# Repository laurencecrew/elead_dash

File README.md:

# elead_dash

Dash module for Honda Lead scooter electric conversion.

Based on STM32Duino for STM32F103C8T6

Design includes:
- Votol EM150SP 'CANbus' controller
- Daly R25A-GI02 BMS CANBus x 2
- SSD1306 OLED 64x48 0.66" SPI x 2
- Original fuel gauge driven by H-bridge / PWM
- See also, elead_lighting for tail light module

See 'Hardware' folder for:
- Bike wiring diagram
- PCB schematics
- Eagle files
- PCB CAM outputs

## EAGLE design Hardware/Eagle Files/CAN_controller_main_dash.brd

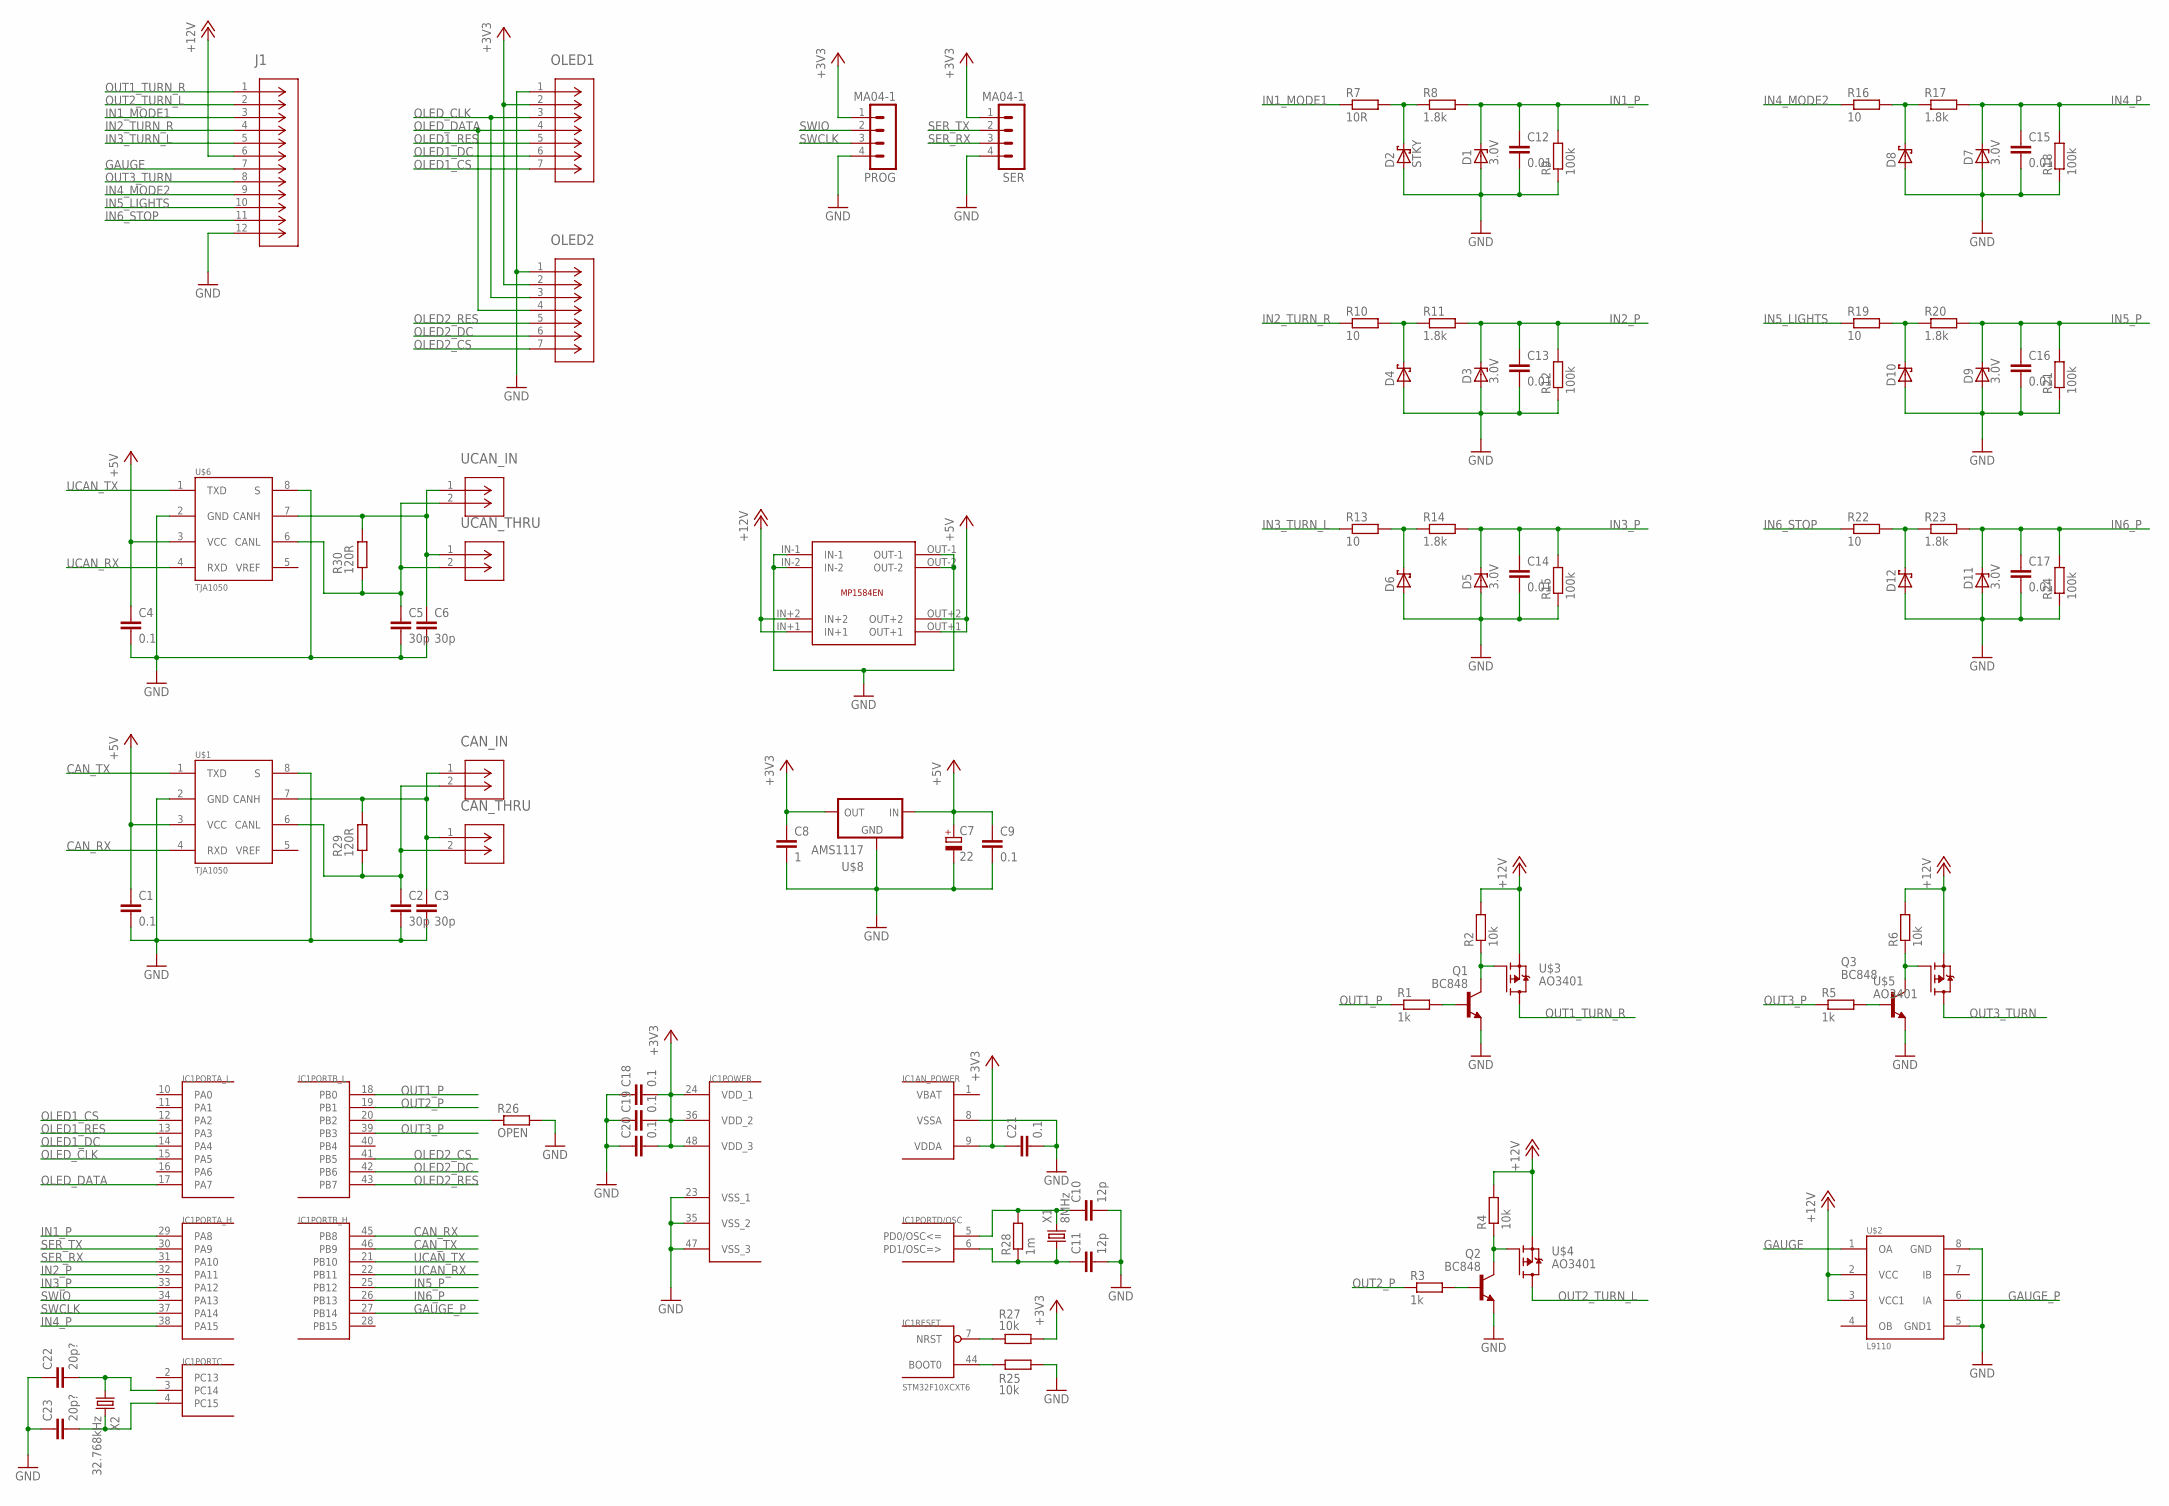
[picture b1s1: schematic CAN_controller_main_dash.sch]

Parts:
C1, C4, C9, C18, C19, C20, C21: 0.1; C0603
C2, C3, C5, C6: 30p; C0603
C7: 22; A/3216-18R
C8: 1; C0805
C10, C11: 12p; C0603
C12, C13, C14, C15, C16, C17: 0.01; C0603
C22, C23: 20p?; C0603
CAN_IN: CAN_IN; CON_2068320202_MOL
CAN_THRU: MOLEX_2068320202; CON_2068320202_MOL
D1, D3, D5, D7, D9, D11: 3.0V; ZD0603
D2: STKY; ZD0603
D4, D6, D8, D10, D12: DIODE_SCHOTTKY; ZD0603
IC1: STM32F10XCXT6; TQFP48
J1: MOLEX_2068321202; CON_2068321202_MOL
OLED1, OLED2: MOLEX_1053091107; CON_1053091107
PROG: MA04-1; 1X04
Q1, Q2, Q3: BC848; SOT23
R1, R3, R5: 1k; R0603
R2, R4, R6, R25, R27: 10k; R0603
R7: 10R; R0603
R8, R11, R14, R17, R20, R23: 1.8k; R0603
R9, R12, R15, R18, R21, R24: 100k; R0603
R10, R13, R16, R19, R22: 10; R0603
R26: OPEN; R0603
R28: 1m; R0603
R29, R30: 120R; R0603
SER: MA04-1; 1X04
U$1, U$6: TJA1050; SO08
U$2: L9110; SO08
U$3, U$4, U$5: AO3401; SOT23
U$7: MP1584_DC-DC_MODULEMINI_22X17; MP1584_DC-DC_MODULE
U$8: AMS1117; SOT223-W
UCAN_IN: MOLEX_2068320202; CON_2068320202_MOL
UCAN_THRU: MOLEX_2068320202; CON_2068320202_MOL
X1: 8MHz; XTAL-ECX-53
X2: 32.768kHz; MM20SS

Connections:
+3V3: C8.1, C18.2, C19.2, C20.2, C21.1, IC1.9 (VDDA), IC1.24 (VDD_1), IC1.36 (VDD_2), IC1.48 (VDD_3), OLED1.2, OLED2.2, PROG.1, R27.2, SER.1, U$8.2 (OUT)
+5V: C1.1, C4.1, C7.+, C9.1, U$1.3 (VCC), U$6.3 (VCC), U$7.OUT+1, U$7.OUT+2, U$8.3 (IN)
+12V: J1.6, R2.2, R4.2, R6.2, U$2.2 (VCC), U$2.3 (VCC1), U$3.2 (S), U$4.2 (S), U$5.2 (S), U$7.IN+1, U$7.IN+2
CANH: C3.1, CAN_IN.1, CAN_THRU.1, R29.2, U$1.7 (CANH)
CANL: C2.1, CAN_IN.2, CAN_THRU.2, R29.1, U$1.6 (CANL)
CAN_RX: IC1.45 (PB8), U$1.4 (RXD)
CAN_TX: IC1.46 (PB9), U$1.1 (TXD)
GAUGE: J1.7, U$2.1 (OA)
GAUGE_P: IC1.27 (PB14), U$2.6 (IA)
GND: C1.2, C2.2, C3.2, C4.2, C5.2, C6.2, C7.-, C8.2, C9.2, C10.2, C11.2, C12.2, C13.2, C14.2, C15.2, C16.2, C17.2, C18.1, C19.1, C20.1, C21.2, C22.1, C23.1, D1.A, D2.A, D3.A, D4.A, D5.A, D6.A, D7.A, D8.A, D9.A, D10.A, D11.A, D12.A, IC1.8 (VSSA), IC1.23 (VSS_1), IC1.35 (VSS_2), IC1.47 (VSS_3), J1.12, OLED1.1, OLED2.1, PROG.4, Q1.2 (E), Q2.2 (E), Q3.2 (E), R9.1, R12.1, R15.1, R18.1, R21.1, R24.1, R25.2, R26.2, SER.4, U$1.2 (GND), U$1.8 (S), U$2.5 (GND1), U$2.8 (GND), U$6.2 (GND), U$6.8 (S), U$7.IN-1, U$7.IN-2, U$7.OUT-1, U$7.OUT-2, U$8.1 (GND)
IN1_MODE1: J1.3, R7.1
IN1_P: C12.1, D1.C, IC1.29 (PA8), R8.2, R9.2
IN2_P: C13.1, D3.C, IC1.32 (PA11), R11.2, R12.2
IN2_TURN_R: J1.4, R10.1
IN3_P: C14.1, D5.C, IC1.33 (PA12), R14.2, R15.2
IN3_TURN_L: J1.5, R13.1
IN4_MODE2: J1.9, R16.1
IN4_P: C15.1, D7.C, IC1.38 (PA15), R17.2, R18.2
IN5_LIGHTS: J1.10, R19.1
IN5_P: C16.1, D9.C, IC1.25 (PB12), R20.2, R21.2
IN6_P: C17.1, D11.C, IC1.26 (PB13), R23.2, R24.2
IN6_STOP: J1.11, R22.1
unnamed: Q2.1 (B), R3.2
unnamed: Q2.3 (C), R4.1, U$4.1 (G)
unnamed: Q3.1 (B), R5.2
unnamed: Q1.1 (B), R1.2
unnamed: Q1.3 (C), R2.1, U$3.1 (G)
unnamed: Q3.3 (C), R6.1, U$5.1 (G)
unnamed: C10.1, IC1.5 (PD0/OSC<=), R28.2, X1.2
unnamed: C11.1, IC1.6 (PD1/OSC=>), R28.1, X1.1
unnamed: D2.C, R7.2, R8.1
unnamed: IC1.44 (BOOT0), R25.1
unnamed: D4.C, R10.2, R11.1
unnamed: IC1.20 (PB2), R26.1
unnamed: IC1.7 (NRST), R27.1
unnamed: D6.C, R13.2, R14.1
unnamed: C22.2, IC1.3 (PC14), X2.1
unnamed: C23.2, IC1.4 (PC15), X2.4 (2)
unnamed: D8.C, R16.2, R17.1
unnamed: D10.C, R19.2, R20.1
unnamed: D12.C, R22.2, R23.1
OLED1_CS: IC1.12 (PA2), OLED1.7
OLED1_DC: IC1.14 (PA4), OLED1.6
OLED1_RES: IC1.13 (PA3), OLED1.5
OLED2_CS: IC1.41 (PB5), OLED2.7
OLED2_DC: IC1.42 (PB6), OLED2.6
OLED2_RES: IC1.43 (PB7), OLED2.5
OLED_CLK: IC1.15 (PA5), OLED1.3, OLED2.3
OLED_DATA: IC1.17 (PA7), OLED1.4, OLED2.4
OUT1_P: IC1.18 (PB0), R1.1
OUT1_TURN_R: J1.1, U$3.3 (D)
OUT2_P: IC1.19 (PB1), R3.1
OUT2_TURN_L: J1.2, U$4.3 (D)
OUT3_P: IC1.39 (PB3), R5.1
OUT3_TURN: J1.8, U$5.3 (D)
SER_RX: IC1.31 (PA10), SER.3
SER_TX: IC1.30 (PA9), SER.2
SWCLK: IC1.37 (PA14), PROG.3
SWIO: IC1.34 (PA13), PROG.2
UCANH: C6.1, R30.2, U$6.7 (CANH), UCAN_IN.1, UCAN_THRU.1
UCANL: C5.1, R30.1, U$6.6 (CANL), UCAN_IN.2, UCAN_THRU.2
UCAN_RX: IC1.22 (PB11), U$6.4 (RXD)
UCAN_TX: IC1.21 (PB10), U$6.1 (TXD)
VBAT: IC1.1 (VBAT)

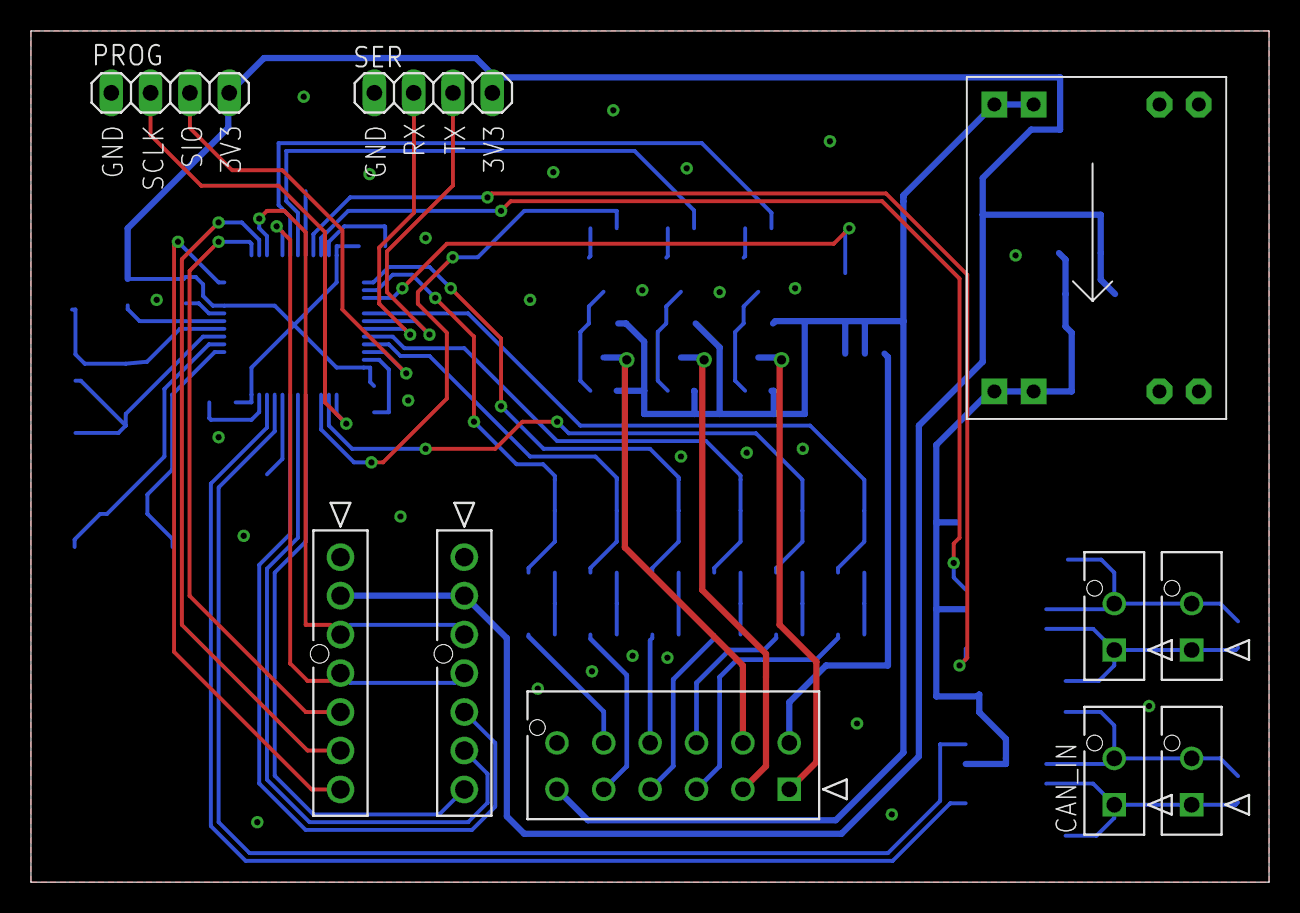
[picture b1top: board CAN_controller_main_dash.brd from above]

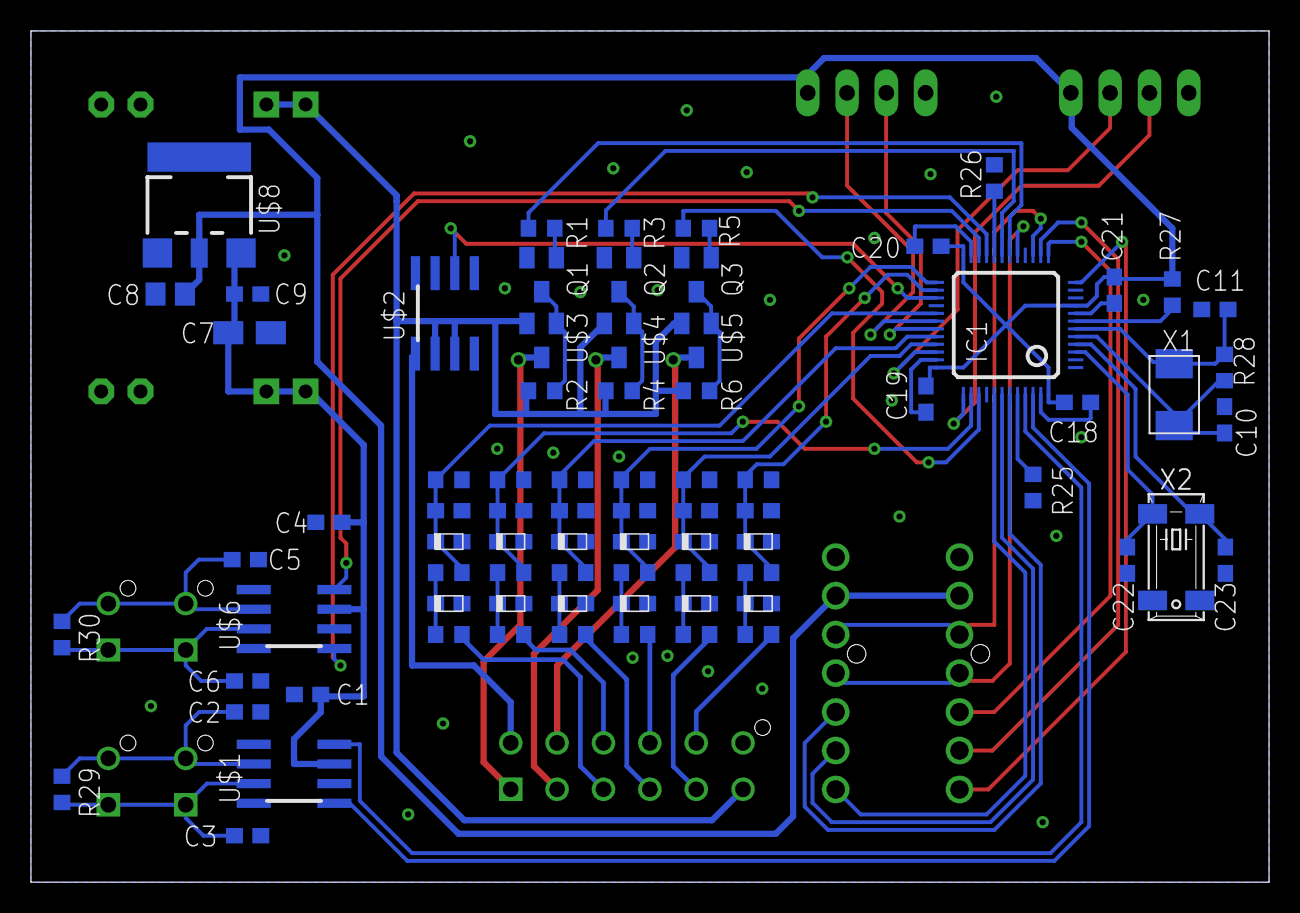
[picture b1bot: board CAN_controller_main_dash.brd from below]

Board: 2 copper layers, 80.0 x 55.0 mm, 88 parts (78 on the bottom side), 63 nets.

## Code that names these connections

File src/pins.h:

#ifndef PINS_H
#define PINS_H

#define DEBUG_USART     USART1  // TX1: PA9 RX1: PA10
#define VOTOL_USART     USART3  // TX3: PB10 RX3: PB11

#define CAN_REMAP        2   // CAN_RX mapped to PB8, CAN_TX mapped to PB9 (not available on 36-pin package)

#define OLED_DC_1       PB6
#define OLED_CS_1       PB5 
#define OLED_RESET_1    PB7

#define OLED_DC_2       PA4
#define OLED_CS_2       PA2  
#define OLED_RESET_2    PA3

#define LIGHTS_IN       PB12
#define TURN_L_IN       PA12
#define TURN_R_IN       PA11
#define BRAKE_IN        PB13

#define MODE_1_IN       PA8
#define MODE_2_IN       PA15

#define TURN_L_OUT      PB1
#define TURN_R_OUT      PB0
#define TURN_IND_OUT    PB3
#define GAUGE_PWM       PB14

#endif

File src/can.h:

// Adapted from
// https://github.com/nopnop2002/Arduino-STM32-CAN
//
  
#ifndef CAN_H_INCLUDED
#define CAN_H_INCLUDED

#include <Arduino.h>

#define CAN_DEBUG 0

#define STM32_CAN_TIR_TXRQ              (1U << 0U)  // Bit 0: Transmit Mailbox Request
#define STM32_CAN_RIR_RTR               (1U << 1U)  // Bit 1: Remote Transmission Request
#define STM32_CAN_RIR_IDE               (1U << 2U)  // Bit 2: Identifier Extension
#define STM32_CAN_TIR_RTR               (1U << 1U)  // Bit 1: Remote Transmission Request
#define STM32_CAN_TIR_IDE               (1U << 2U)  // Bit 2: Identifier Extension

#define CAN_EXT_ID_MASK                 0x1FFFFFFFU
#define CAN_STD_ID_MASK                 0x000007FFU
 
/* Symbolic names for bit rate of CAN message                                */
typedef enum {CAN_50KBPS, CAN_100KBPS, CAN_125KBPS, CAN_250KBPS, CAN_500KBPS, CAN_1000KBPS} BITRATE;

/* Symbolic names for formats of CAN message                                 */
typedef enum {STANDARD_FORMAT = 0, EXTENDED_FORMAT} CAN_FORMAT;

/* Symbolic names for type of CAN message                                    */
typedef enum {DATA_FRAME = 0, REMOTE_FRAME}         CAN_FRAME;

typedef struct
{
  uint32_t id;        /* 29 bit identifier                               */
  uint8_t  data[8];   /* Data field                                      */
  uint8_t  len;       /* Length of data field in bytes                   */
  uint8_t  ch;        /* Object channel(Not use)                         */
  uint8_t  format;    /* 0 - STANDARD, 1- EXTENDED IDENTIFIER            */
  uint8_t  type;      /* 0 - DATA FRAME, 1 - REMOTE FRAME                */
} CAN_msg_t;

typedef const struct
{
  uint8_t TS2;
  uint8_t TS1;
  uint8_t BRP;
} CAN_bit_timing_config_t;


/**
 * Print registers.
*/ 
void printRegister(char * buf, uint32_t reg);

/**
 * Initializes the CAN filter registers.
 *
 * @preconditions   - This register can be written only when the filter initialization mode is set (FINIT=1) in the CAN_FMR register.
 * @params: index   - Specified filter index. index 27:14 are available in connectivity line devices only.
 * @params: scale   - Select filter scale.
 *                    0: Dual 16-bit scale configuration
 *                    1: Single 32-bit scale configuration
 * @params: mode    - Select filter mode.
 *                    0: Two 32-bit registers of filter bank x are in Identifier Mask mode
 *                    1: Two 32-bit registers of filter bank x are in Identifier List mode
 * @params: fifo    - Select filter assigned.
 *                    0: Filter assigned to FIFO 0
 *                    1: Filter assigned to FIFO 1
 * @params: bank1   - Filter bank register 1
 * @params: bank2   - Filter bank register 2
 *
 */
void CANSetFilter(uint8_t index, uint8_t scale, uint8_t mode, uint8_t fifo, uint32_t bank1, uint32_t bank2);

/**
 * Initializes the CAN controller with specified bit rate.
 *
 * @params: bitrate - Specified bitrate. If this value is not one of the defined constants, bit rate will be defaulted to 125KBS
 * @params: remap   - Select CAN port. 
 *                    =0:CAN_RX mapped to PA11, CAN_TX mapped to PA12
 *                    =1:Not used
 *                    =2:CAN_RX mapped to PB8, CAN_TX mapped to PB9 (not available on 36-pin package)
 *                    =3:CAN_RX mapped to PD0, CAN_TX mapped to PD1 (available on 100-pin and 144-pin package)
 *
 */
bool CANInit(BITRATE bitrate, int remap);

/**
 * Decodes CAN messages from the data registers and populates a 
 * CAN message struct with the data fields.
 * 
 * @preconditions A valid CAN message is received
 * @params CAN_rx_msg - CAN message structure for reception
 * 
 */
void CANReceive(CAN_msg_t* CAN_rx_msg);
 
/**
 * Encodes CAN messages using the CAN message struct and populates the 
 * data registers with the sent.
 * 
 * @params CAN_tx_msg - CAN message structure for transmission
 * 
 */
void CANSend(CAN_msg_t* CAN_tx_msg);

 /**
 * Returns whether there are CAN messages available.
 *
 * @returns If pending CAN messages are in the CAN controller
 *
 */
uint8_t CANMsgAvail(void);


#endif

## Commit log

2022-11-08 add all
2022-11-08 Add SSD1306 modified library
2022-11-08 Removed other libraries etc
2022-11-08 Part implemented trip and stats
2022-11-08 Fixed string buffer size; renamed avg_speed_x10
2022-11-20 Moved Votol and BMS globals to modules
2022-11-21 Fixed Votol startup bug, new flush_rx function
2022-11-21 Fixed Votol startup bug; flush_rx function
2022-11-21 Tidy ups
2022-11-21 Finished tri[p stats; yet to test
2022-11-21 Mode switching, disable interrupts in debounce
2022-11-22 Change Votol readbacks to flush_rx; use TX flush
2022-11-22 Fixed mode switch logic; don't disable interrupts
2023-01-17 Votol resp to trip / stats screens for sport mode
2023-01-17 Fix amps display for small values
2023-01-20 Added Hardware folder and updated Readme
2023-01-20 Moved rear lighting Hardware files to own repo
2023-03-12 Attempt to fix wh/km bug (distance_mm to int32)
2023-03-12 Clear trip stats only on power cycle
2023-05-09 Save, load and reset stats
2023-05-09 Added eedata module UNTESTED
2023-05-09 Update date
2025-07-25 Show VOTOL fault code on display
2026-02-21 Added fault codes to voltol_em.h
2026-02-21 Typo

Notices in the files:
parts and their libraries:
COPYRIGHT: Copyright (C) 2022 Ultra Librarian. All rights reserved.
